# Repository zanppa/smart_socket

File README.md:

# smart_socket
A "smart" remote controlled power socket

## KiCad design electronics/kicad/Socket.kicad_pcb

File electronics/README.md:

This directory contains the electronics design files

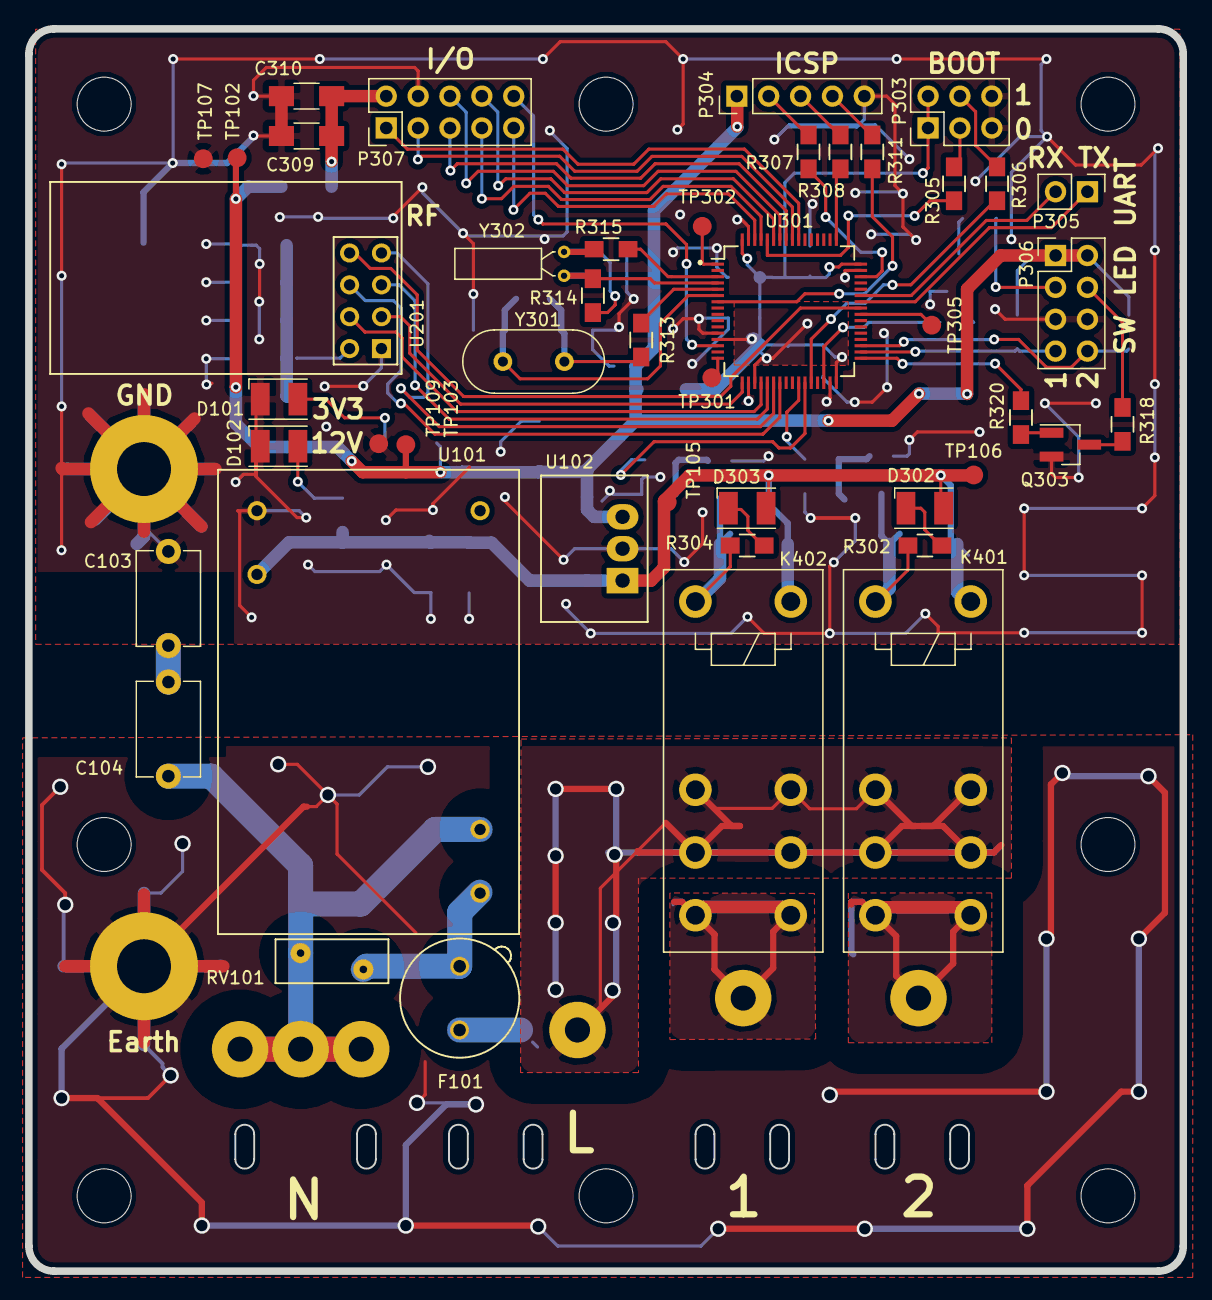
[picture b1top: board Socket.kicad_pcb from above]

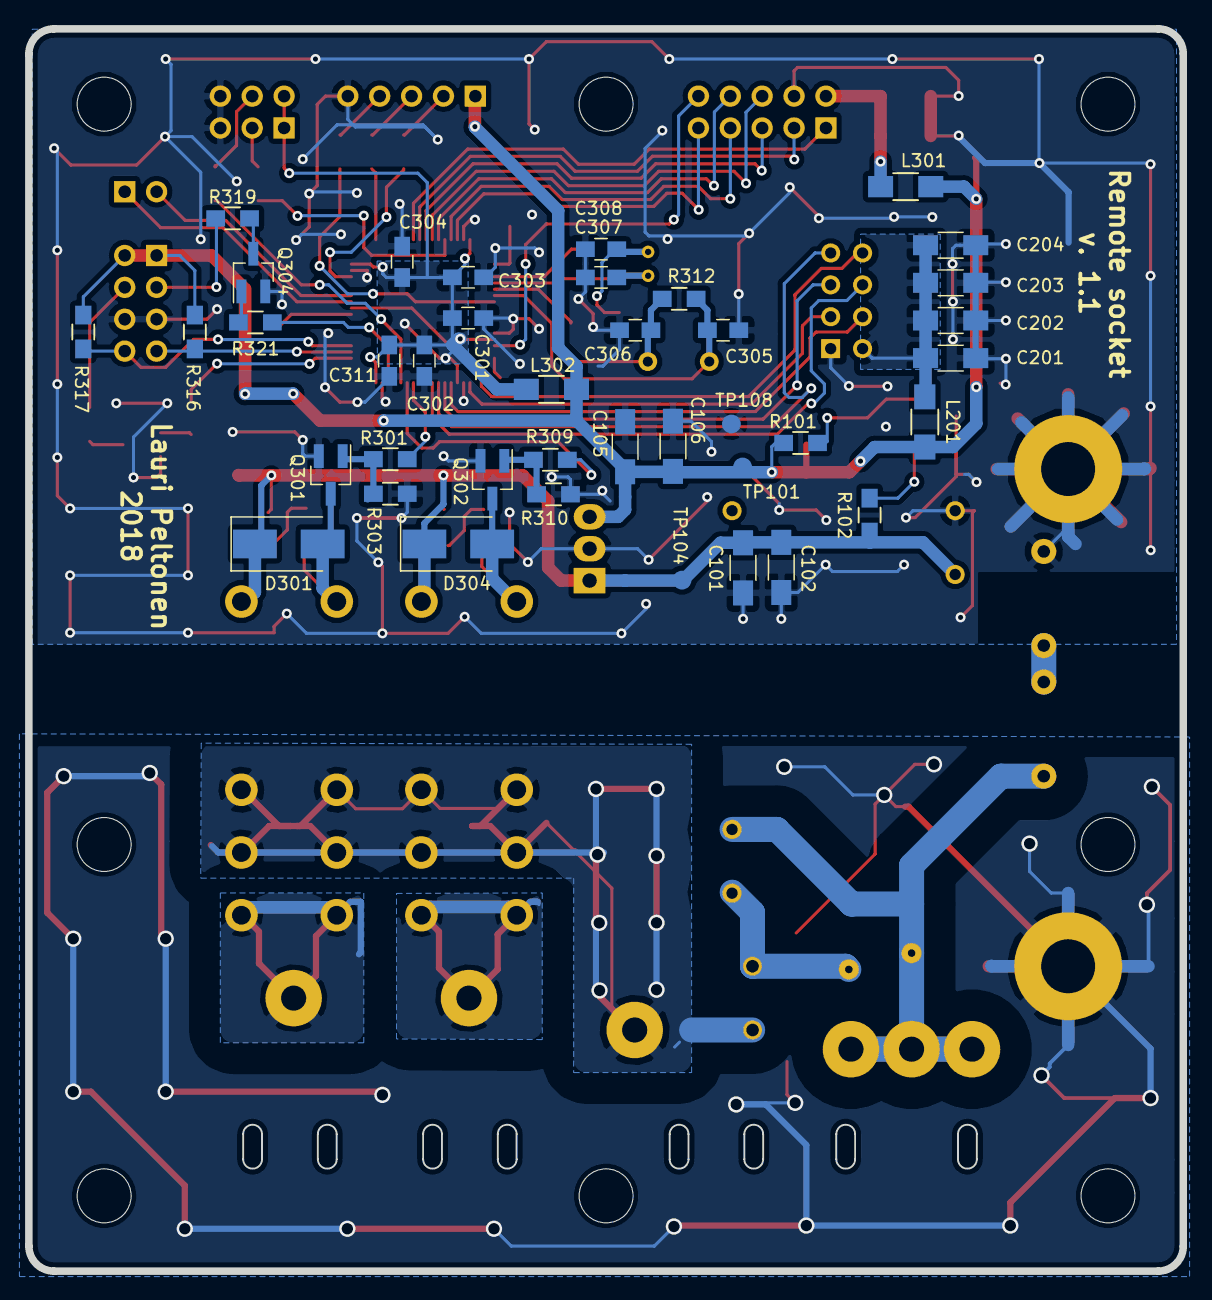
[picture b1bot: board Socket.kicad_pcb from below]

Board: 2 copper layers, 92.0 x 99.0 mm, 100 parts (39 on the bottom side), 67 nets.

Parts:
C101, C102, C105, C106, C309, C310: 10u; C_1206_HandSoldering
C103, C104: 2.2nF 3kVDC Y; C_Disc_D7.5mm_W5.0mm_P7.50mm
C201, C202, C203, C204: 10u X7R; C_1206_HandSoldering
C301, C302, C303, C304, C311: 100n; C_0805_HandSoldering
C305, C306: 40p; C_0805_HandSoldering
C307, C308: 8p; C_0805_HandSoldering
D101, D102, D302, D303: LED; LED_PLCC-2
D301, D304: D; D_SMB_Handsoldering
F101: Fuse; Fuseholder_Fuse_TR5_Littlefuse-No560_No460
J101, J102: Screw_Terminal_1x01; MountingHole_4.3mm_M4_Pad
K401, K402: GZSH-12V; Relay_SPDT_Goodsky_GZ
L201, L301, L302: Ferrite_Bead_Small; R_1206_HandSoldering
MK101, MK102, MK103, MK104, MK105, MK106, MK107, MK108: Mounting_Hole; MountingHole_4.3mm_M4
P101, P102, P103, P104, P301, P302: CONN_01X01; SolderWirePad_single_2mmDrill
P303: CONN_02X03; Pin_Header_Straight_2x03_Pitch2.54mm
P304: CONN_01X05; Pin_Header_Straight_1x05_Pitch2.54mm
P305: CONN_01X02; Pin_Header_Straight_1x02_Pitch2.54mm
P306: CONN_01X10; Pin_Header_Straight_2x04_Pitch2.54mm
P307: CONN_01X10; Pin_Header_Straight_2x05_Pitch2.54mm
Q301, Q302, Q303, Q304: BC817; SOT-23_Handsoldering
R101: 1.13k; R_0805_HandSoldering
R102, R302, R303, R304, R310, R320, R321: 10k; R_0805_HandSoldering
R301, R309: 1k; R_0805_HandSoldering
R305, R306: 100k; R_0805_HandSoldering
R307, R308, R311, R318, R319: 100; R_0805_HandSoldering
R312, R314: 1M*; R_0805_HandSoldering
R313, R315: 0; R_0805_HandSoldering
R316, R317: 4.7k; R_0805_HandSoldering
RV101: EPCOS S14 < 1kV?; RV_Disc_D9_W3.5_P5
TP101, TP102, TP103, TP104, TP105, TP106, TP107, TP108, TP109, TP301, TP305: TEST; Measurement_Point_Round-SMD-Pad_Small
TP302: Vbat; Measurement_Point_Round-SMD-Pad_Small
U101: IRM-03-12; IRM-03
U102: R-78E3.3-0.5; R-78
U201: nRF24L01_module
U301: STM32F103R4Tx; LQFP-64_10x10mm_Pitch0.5mm
Y301: 8.000MHz; Crystal_HC18-U_Vertical
Y302: 32.768k; Crystal_C26-LF_d2.1mm_l6.5mm_Horizontal

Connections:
+5V: C105.1, C106.1, L201.1, L301.1, L302.1, P304.1, P306.1, P306.2, R101.1, R316.1, R317.1, TP101.1, TP102.1, TP103.1, U102.3
+12V: C101.1, C102.1, D301.1, D302.2, D303.2, D304.1, K401.A1, K402.A1, R102.1, TP104.1, TP105.1, TP106.1, U101.3, U102.1
/Ctrl1: R301.2, U301.26
/Ctrl2: R309.2, U301.27
/L_fused: F101.2, RV101.2, U101.1
/Mid: C103.1, C104.2
/Processor/OSC32IN: R315.1, U301.3
/Processor/OSC32OUT: C307.1, R314.2, U301.4, Y302.2
/Processor/OSCIN: R313.1, U301.5
/Processor/OSCOUT: C305.1, R312.2, U301.6, Y301.1
/Processor/PA0: P307.10, U301.14
/Processor/PA2: TP301.1, U301.16
/Processor/PB3: P307.1, U301.55
/Processor/PB4: P307.3, U301.56
/Processor/PB5: P307.5, U301.57
/Processor/PB6: P307.6, U301.58
/Processor/PB7: P307.8, U301.59
/Processor/PB8: P307.7, U301.61
/Processor/PB9: P307.9, U301.62
/Processor/PB11: R321.1, U301.30
/Processor/PB12: R320.1, U301.33
/Processor/PB13: P306.7, R316.2, U301.34
/Processor/PB14: P306.8, R317.2, U301.35
/Processor/PC9: TP305.1, U301.40
/Processor/UART1_RX: P305.2, U301.43
/Processor/UART1_TX: P305.1, U301.42
/Processor/XTAL11: C306.1, R312.1, R313.2, Y301.2
/Processor/XTAL21: C308.1, R314.1, R315.2, Y302.1
/Processor/boot0: R305.2, U301.60
/Processor/boot0con: P303.3, R305.1
/Processor/boot1: R306.1, U301.28
/Processor/boot1con: P303.4, R306.2
/Processor/led1: P306.3, R319.2
/Processor/led2: P306.4, R318.2
/Processor/nrst: R311.2, U301.7
/Processor/nrstcon: P304.4, R311.1
/Processor/swdclk: R308.2, U301.49
/Processor/swdclkcon: P304.3, R308.1
/Processor/swdio: R307.2, U301.46
/Processor/swdiocon: P304.2, R307.1
/Processor/vbat: TP302.1, U301.1
/Processor/vdd_filt: C301.1, C302.1, C303.1, C304.1, C311.1, L302.2, P303.1, P303.2, U301.13, U301.19, U301.32, U301.48, U301.64
/Processor/vdd_io: C309.1, C310.1, L301.2, P307.2
/RF/rfPWR_filt: C201.1, C202.1, C203.1, C204.1, L201.2, U201.2
/Relays/Lout1: K401.14, K401.24, P301.1
/Relays/Lout2: K402.14, K402.24, P302.1
/Relays/Relay1: D301.2, K401.A2, Q301.3, R302.2
/Relays/Relay2: D304.2, K402.A2, Q302.3, R304.2
/rfCE: U201.3, U301.17
/rfCSK: U201.5, U301.21
/rfCSN: U201.4, U301.20
/rfIRQ: U201.8, U301.41
/rfMISO: U201.7, U301.22
/rfMOSI: U201.6, U301.23
GND: C101.2, C102.2, C103.2, C105.2, C106.2, C201.2, C202.2, C203.2, C204.2, C301.2, C302.2, C303.2, C304.2, C305.2, C306.2, C307.2, C308.2, C309.2, C310.2, C311.2, D101.1, D102.1, J102.1, P303.5, P303.6, P304.5, P306.5, P306.6, P307.4, Q301.2, Q302.2, Q303.2, Q304.2, R303.1, R310.1, TP107.1, TP108.1, TP109.1, U101.4, U102.2, U201.1, U301.12, U301.18, U301.31, U301.47, U301.63
GNDPWR: C104.1, P102.1, P103.1, P104.1, RV101.1, U101.2
HT: F101.1, K401.11, K401.12, K401.21, K401.22, K402.11, K402.12, K402.21, K402.22, P101.1
unnamed: D101.2, R101.2
unnamed: D102.2, R102.2
unnamed: D302.1, R302.1
unnamed: D303.1, R304.1
unnamed: Q301.1, R301.1, R303.2
unnamed: Q302.1, R309.1, R310.2
unnamed: Q303.1, R320.2
unnamed: Q303.3, R318.1
unnamed: Q304.1, R321.2
unnamed: Q304.3, R319.1
